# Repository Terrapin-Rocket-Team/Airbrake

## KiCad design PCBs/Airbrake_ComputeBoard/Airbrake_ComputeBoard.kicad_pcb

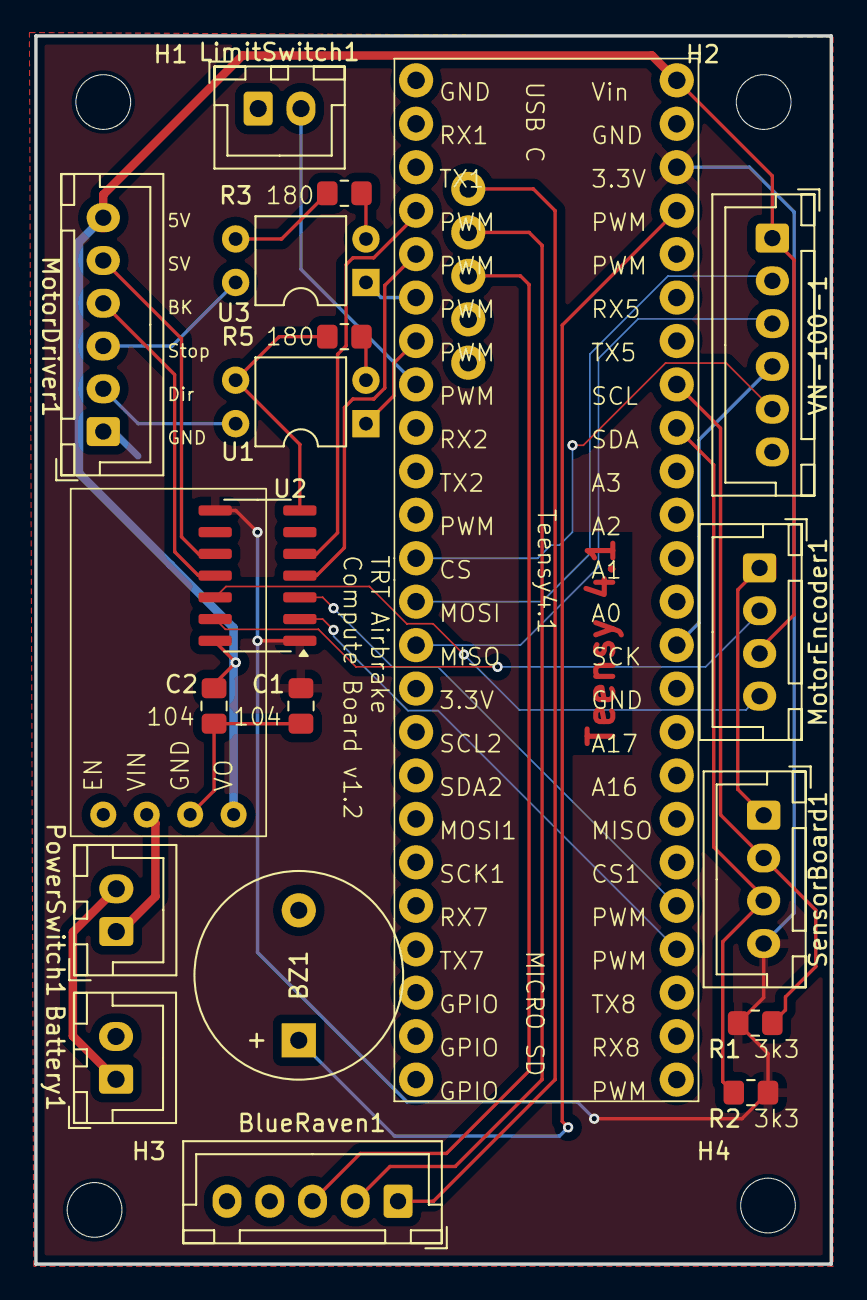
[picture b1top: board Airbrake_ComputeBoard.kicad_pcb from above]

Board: 2 copper layers, 46.5 x 71.8 mm, 24 parts (0 on the bottom side), 30 nets.

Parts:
BZ1: Buzzer; Buzzer_12x9.5RM7.6
Battery1: Conn_01x02; JST_XH_B2B-XH-A_1x02_P2.50mm_Vertical
BlueRaven1: Conn_01x05; JST_XH_B5B-XH-A_1x05_P2.50mm_Vertical
Buck_Converter1: Buck_Converter
C1, C2: 0.1µF; C_0805_2012Metric_Pad1.18x1.45mm_HandSolder
H1, H2, H3, H4: MountingHole; MountingHole_3.2mm_M3
LimitSwitch1: Conn_01x02; JST_XH_B2B-XH-A_1x02_P2.50mm_Vertical
MotorDriver1: Conn_01x06; JST_XH_B6B-XH-A_1x06_P2.50mm_Vertical
MotorEncoder1: Conn_01x04; JST_XH_B4B-XH-A_1x04_P2.50mm_Vertical
PowerSwitch1: Conn_01x02; JST_XH_B2B-XH-A_1x02_P2.50mm_Vertical
R1, R2: 3.3kΩ; R_0805_2012Metric_Pad1.20x1.40mm_HandSolder
R3, R5: 180Ω; R_0805_2012Metric_Pad1.20x1.40mm_HandSolder
SensorBoard1: Conn_01x04; JST_XH_B4B-XH-A_1x04_P2.50mm_Vertical
Teensy4.1: Teensy_4.1_USB
U1, U3: PC817; DIP-4_W7.62mm
U2: TXB0104D; SOIC-14_3.9x8.7mm_P1.27mm
VN-100-1: Conn_01x06; JST_XH_B6B-XH-A_1x06_P2.50mm_Vertical

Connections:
+3.3V: C1.1, R1.2, R2.1, SensorBoard1.4, Teensy4.1.45 (3.3V), U2.1 (VCCA), U2.8 (OE)
+5V: Buck_Converter1.3 (VO), C2.1, MotorDriver1.6, MotorEncoder1.3, Teensy4.1.47 (Vin), U2.14 (VCCB), VN-100-1.1
/BK: Teensy4.1.4 (PWM), U2.4 (A3)
/BK_5V: MotorDriver1.4, U2.11 (B3)
/CS: Teensy4.1.11 (CS), VN-100-1.5
/D+: BlueRaven1.3, Teensy4.1.50 (usb_D+)
/D-: BlueRaven1.2, Teensy4.1.49 (usb_D-)
/Dir: Teensy4.1.6 (PWM), U1.1
/Dir_5V: MotorDriver1.2, U1.4
/Encoder_A: Teensy4.1.27 (PWM), U2.2 (A1)
/Encoder_A_5V: MotorEncoder1.2, U2.13 (B1)
/Encoder_B: Teensy4.1.28 (PWM), U2.3 (A2)
/Encoder_B_5V: MotorEncoder1.4, U2.12 (B2)
/Limit_Switch: LimitSwitch1.2, Teensy4.1.7 (PWM)
/MISO: Teensy4.1.13 (MISO), VN-100-1.3
/MOSI: Teensy4.1.12 (MOSI), VN-100-1.2
/SCK: Teensy4.1.34 (SCK), VN-100-1.4
/SCL: R1.1, SensorBoard1.2, Teensy4.1.40 (SCL)
/SDA: R2.2, SensorBoard1.3, Teensy4.1.39 (SDA)
/SV: Teensy4.1.3 (PWM), U2.5 (A4)
/SV_5V: MotorDriver1.5, U2.10 (B4)
/Stop: Teensy4.1.5 (PWM), U3.1
/Stop_5V: MotorDriver1.3, U3.4
/buzzer: BZ1.1 (+), Teensy4.1.44 (PWM)
/usb_5v: BlueRaven1.1, Teensy4.1.48 (usb_5v)
GND: BZ1.2 (-), Battery1.2, BlueRaven1.4, BlueRaven1.5, Buck_Converter1.2 (GND), C1.2, C2.2, LimitSwitch1.1, MotorDriver1.1, MotorEncoder1.1, R3.2, R5.2, SensorBoard1.1, Teensy4.1.0 (GND), Teensy4.1.46 (GND), Teensy4.1.51 (GND), Teensy4.1.52 (GND), U1.3, U2.7 (GND), U3.3, VN-100-1.6
unnamed: Battery1.1, PowerSwitch1.2
unnamed: Buck_Converter1.1 (VIN), PowerSwitch1.1
unnamed: R3.1, U3.2
unnamed: R5.1, U1.2

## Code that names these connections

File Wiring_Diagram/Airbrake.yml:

connectors:
  BlueRaven1:
    type: Compute Board
    subtype: Male
    pincount: 5
    pinlabels: [usb_5v, D-, D+, GND, GND]
    image:
      src: Pictures/BlueRaven1.png
      height: 100


  SensorBoard1:
    type: Compute Board
    subtype: Male
    pincount: 4
    pinlabels: [GND, SCL, SDA, +3.3V]
    image:
      src: Pictures/SensorBoard1.png
      height: 100


  MotorEncoder1:
    type: Compute Board
    subtype: Male
    pincount: 4
    pinlabels: [GND, Encoder_A, +5V, Encoder_B]
    image:
      src: Pictures/MotorEncoder1.png
      height: 100


  VN-100-1:
    type: compute Board
    subtype: Male
    pincount: 6
    pinlabels: [+5V, MOSI, MISO, SCK, SC, GND]
    image:
      src: Pictures/VN-100.png
      height: 100


  LimitSwitch1:
    type: Compute Board
    subtype: Male
    pincount: 3
    pinlabels: [GND, NC, NO]
    image:
      src: Pictures/LimitSwitch1.png
      height: 100


  MotorDriver1:
    type: Compute Board
    subtype: Male
    pincount: 6
    pinlabels: [GND, Motordriver_pin_2, Motordriver_pin_3, Motordriver_pin_4, Motordriver_pin_5, +5V]
    image:
      src: Pictures/MotorDriver1.png
      height: 100


  Battery1:
    pincount: 2
    pinlabels: [NET - (Battery1-Pin_1), GND]
    image:
      src: Pictures/Battery1.png
      height: 100
  

  PowerSwitch1:
    pincount: 2
    pinlabels: [GND, +V]


  BlueRaven:
    type: Sensor
    subtype: Micro-USB / Screw
    pincount: 7
    pinlabels: [+V, GND, APO, MAIN, 3RD, 4TH, Micro-USB]
    image:
      src: Pictures/BlueRaven.png
      height: 100


  SensorBoard:
    type: Sensor
    subtype: Male
    pincount: 4
    pinlabels: [GND, SCL, SDA, 3V3]
    image:
      src: Pictures/SensorBoard.png
      height: 80


  MotorController_IN:
    type: Controler
    subtype: Screw
    pincount: 6
    pinlabels: [5V, 0-5V, GND, DIR, BRAKE, STOP]
    image:
      src: Pictures/MotorControlerIn.png
      height: 160  # Scale the image size slightly down


  MotorController_OUT3:
    type: Controler
    subtype: Screw
    pincount: 3
    pinlabels: [MA, BA, MC]
    image:
      src: Pictures/MotorControlerOut.png
      height: 110  # Scale the image size slightly down
    

  MotorController_OUT2:
    type: Controler
    subtype: Screw
    pincount: 2
    pinlabels: [VCC, GND]
    image:
      src: Pictures/MotorControlerOut.png
      height: 110

  

  MotorController_OUT5:
    type: Controler
    subtype: pin
    pincount: 5
    pinlabels: [GND, Hc, Hb, Ha, 5V]
    image:
      src: Pictures/MotorController_Out5.png
      height: 70


  VN-100_J5:
    type: Sensor
    subtype: Male
    pincount: 30
    pinlabels: [GND, GND, GND, GND, TX2, RX2, TARE/RESTORE, NC, SYNC_OUT, WIN, ENABLE, TX1, RX1, RESV, SYNC_IN_2, SPI_SCK, SPI_MISO, REPRGM, NRST, SYNC_IN, SPI_CS, GPS_PPS, VBAT, RESV, RESV, GND, GPS_RF, GND]
    image:
      src: Pictures/Vectornav-100-c.png
      height: 135


  LimitSwitch:
    type: Sensor
    subtype: Clip
    pincount: 3
    pinlabels: [GND, NC, NO]


  Motor3:
    type: Motor
    subtype: Female
    pincount: 3
    pinlabels: [...,...,...]
    image:
      src: Pictures/Motor_connector.png
      height: 100


  Motor5:
    type: Motor
    subtype: Female
    pincount: 5
    pinlabels: [...,...,...,...,...]
    image:
      src: Pictures/Motor_connector.png
      height: 100


  MotorEncoder:
    type: sensor
    subtype: pin
    pincount: 10
    pinlabels: [GND, GND, I, I, A, A, +5V, +5V, B, B]
    image:
      src: Pictures/Motor_encoder.png
      height: 100


  Battery-1:
    pincount: 2
    pinlabels: [+V, GND]
  

  Battery-2:
    pincount: 2
    pinlabels: [+V, GND]


  Battery-3:
    pincount: 2
    pinlabels: [+V, GND]


  Screw_switch1:
    pincount: 2
    pinlabels: [+, -]


  Screw_switch2:
    pincount: 2
    pinlabels: [+, -]


  Screw_switch3:
    pincount: 2
    pinlabels: [+, -]


cables:
  W1:
    colors: [RD, WH, GY, GN, BU]
    wirecount: 5
  W2:
    colors: [BK, YE, LB, RD]
    wirecount: 4
  W3:
    colors: [OG, YE, GN, VT]
    wirecount: 4
    image:
      src: Pictures/Encoder_wire.png
      height: 100
  W4:
    colors: [RD, LB, GN, YE, WH, BK]
    wirecount: 6
  W5:
    colors: [BK,RD]
    wirecount: 2
  W6:
    colors: [YE, YE, LB, WH, YE, BK]
    wirecount: 6
  W7:
    colors: [WH, YE, LB]
    wirecount: 3
    image:
      src: Pictures/Motor_wire3.png
      height: 100
  W8:
    colors: [RD, BK]
    wirecount: 2
  W9:
    colors: [RD, BK]
    wirecount: 2
  W10:
    colors: [BK,LB,YE,OG,RD]
    wirecount: 5
    image:
      src: Pictures/Motor_wire5.png
      height: 100
  W11:
    colors: [RD,BK]
    wirecount: 2
  W12:
    colors: [BK,RD]
    wirecount: 2
  W13:
    colors: [RD,BK]
    wirecount: 2
  W14:
    colors: [RD,BK]
    wirecount: 2


connections:
 -
   - BlueRaven1: [1,2,3,4]
   - W1: [1,2,4,5]
 -
   - W1: [3]
   - BlueRaven: [7]
 -
   - SensorBoard1: [1,2,3,4]
   - W2: [1,2,3,4]
   - SensorBoard: [1,2,3,4]
 -
   - MotorEncoder1: [1,2,3,4]
   - W3: [1,2,3,4]
   - MotorEncoder: [1,5,7,9]
 -
   - VN-100-1: [1,2,3,4,5,6]
   - W4: [1,2,3,4,5,6]
   - VN-100_J5: [10, 17, 19, 16, 23, 18]
 -
   - LimitSwitch1: [1,2]
   - W5: [1,2]
   - LimitSwitch: [1,2]
 -
   - MotorDriver1: [1,2,3,4,5,6]
   - W6: [1,2,3,4,5,6]
 -
   - W6: [2,3,4,5,6]
   - MotorController_IN: [2,5,6,4,3]
 -
   - MotorController_OUT3: [1,2,3]
   - W7: [1,2,3]
   - Motor3: [1,2,3]
 -
   - Battery-1: [1,2] 
   - W8: [1,2]
   - Battery1: [1,2]
 -
   - Battery-2: [1,2]
   - W9: [1,2]
   - Screw_switch1: [1,2]
 -
   - MotorController_OUT5: [1,2,3,4,5]
   - W10: [1,2,3,4,5]
   - Motor5: [1,2,3,4,5]
 - 
   - Screw_switch1: [1,2]
   - W11: [1,2]
   - MotorController_OUT2: [1,2]
 - 
   - PowerSwitch1: [1,2]
   - W12: [1,2]
   - Screw_switch2: [2,1]
 - 
   - Battery-3: [1,2]
   - W13: [1,2]
   - Screw_switch3: [1,2]
 -
   - Screw_switch3: [1,2]
   - W14: [1,2]
   - BlueRaven: [1,2]

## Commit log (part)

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2024-06-21 FlapActuation Optimized Functions
    SAC2024 rewriting air brake code, calculating actuation angle and subsequent functions
2024-07-08 added matlab shock stuff
2024-07-08 initial start
2024-07-18 Basic Cad For New Airbrake
    Not sure if we're going to use it but the rude cad is here
2024-07-23 flap CAD and shock torque calcs
2024-07-29 created motor_parameters
2024-07-29 CAD and dimension updates
2024-08-01 gitignore
2024-08-19 moving flight code to it's own branch
2024-08-28 initial matlab
2024-08-28 added motor and drag simulation
2024-08-28 added aoa. model comleted
2024-08-29 got rid of the .asv
2024-08-31 Moved CAD
2024-09-03 made a rocket type to pass in
2024-09-10 got state estimation tester working with open rocket
2024-09-12 CAD update
2024-09-17 made kf 6 dimension state w/ 3 meas
2024-09-17 added meas data
2024-09-17 got rid of the flight code
2024-09-17 got rid of autosaves
2024-09-17 move motor_parameters to head
2024-09-17 Tentative full CAD config
2024-09-20 flight code that still doesn't build
2024-09-20 Placeholder KF
2024-09-20 Fix State code
2024-09-20 compiled code
2024-09-20 got rid of .DS_Store
2024-09-20 Revert "Moved CAD"
    This reverts commit 17623fdfb91fb210298f1cc3f48321fa1b9009fc.
2024-09-20 Revert "CAD"
    This reverts commit 8359aeebe09319ea7ef6e981cab92fe88a2f2b34.
2024-09-24 h and cpp files
2024-09-24 got rid of binary math
2024-09-24 initail test code
2024-09-24 vn brought into mmfs framework
2024-09-24 added wiring images
2024-09-24 got rid of airbrake cad
2024-09-24 got rid of cad
2024-09-24 compile updates based on mmfs 2.0.0
2024-09-24 added the current cad
2024-09-29 updated airbrake schematic
2024-09-29 created pcb footprint
2024-10-01 CAD updates
2024-10-03 pcb zip
2024-10-06 30k kf sim
2024-10-10 created motor force script
2024-10-11 fixed psi
2024-10-22 Added Teensy footprint with USB headers
2024-10-23 created compute board v1.1
2024-10-23 Updated level shifter transistors w/ resistors
    Added resistors; changed transistors from PNP to NPN; added pull up resistors to output signals.
2024-10-23 Updated PCB to add resistors to level shifters.
    Updated PCB; Added resistors
2024-10-23 final gerber generated
2024-10-24 actual ordered board
2024-10-30 kf stuff
2024-10-30 added the graph of const motor force, var drag force
2024-10-30 make graph say single flap
2024-11-20 made initial encoder class
2024-11-21 encoder updates
2024-11-22 Copied vectornav library into lib folder and added code to read delta time, theta, and velocity
2024-11-22 Added delta V and delta theta code to VN100 mmfs sensor code
2024-12-02 Initial commit to motor branch
2024-12-03 Added packed data code to VN100
2024-12-04 attached vn100 sensor to state
2024-12-04 this isn't working lol
2024-12-04 fix some erros
2024-12-04 baaba
2024-12-04 got compile
2024-12-04 cleaned up and comment airbrake code
2024-12-04 more working
2024-12-05 Added code to control flaps
2024-12-05 added input check to goToDegree
2024-12-05 added some comments
2024-12-07 flight code. vno100 fixes
2024-12-07 dec launch data
2024-12-12 added ability for multiple sensors
2024-12-14 wrote EKF part of readme
2024-12-14 added NEES graph
2024-12-17 Added optocouplers, level shifter, and connector for a limit switch
2024-12-17 Made new PCB
2024-12-19 state estimation stuff
2024-12-19 check and created gerber
2024-12-31 got it working
2025-01-04 serg
2025-01-08 velocity from blueraven
2025-01-09 Include Errors
2025-01-10 All sensor values from Blue Raven
2025-01-29 added blue raven stuff
2025-01-31 Fixed BR
2025-02-01 added a function to stop motor before switching directions
2025-02-01 flight code changes
2025-02-03 airbrake flight code that flew
2025-02-15 updated to mmfs v3.0 for the code
2025-02-18 fixed blowing up altitude
2025-02-18 updating main with contorller code
2025-02-22 added ekf
2025-02-23 compiling on v3
2025-02-23 initial airbrake kalman filter implemented
2025-02-23 added outlier rejection to the kalman filter
    making an mmfs issue for this to be done correctly
2025-02-23 looked over old airbrake functions and added airbrake specific data reporting
2025-02-24 input velocity of calc actuation angle
2025-02-24 Body Frame
2025-02-26 Better BodyFrame
2025-02-26 reviewed body frame transition
2025-02-26 Create Inital_file
2025-02-26 Added files for wiring diagram.
2025-02-26 updated main for first test of baro in HITL
2025-02-28 initial limit switch stuff
2025-02-28 fixed limit switch zeroing problem
2025-02-28 updated zero motor function to the circular buffer thingy
2025-02-28 encoder stuff
2025-02-28 MotorStopCondition
2025-03-01 updated stop to stall condition. can't have limit switch prevent moving flaps out
2025-03-01 shit is breaking
2025-03-01 set max flap angle to 70 and fixed crashing
2025-03-02 changed for hitl over serial
2025-03-02 basic changes from HITL branch
2025-03-02 75 to 70
2025-03-02 some changes
2025-03-03 code we flew in the march mdra launch
2025-03-07 hitl updates
2025-03-07 compiles
2025-03-07 propagator
2025-03-07 made some simulation updates
2025-03-07 got a good bit of the sim code done
2025-03-10 Added code to prevent NaN values and replace them with approximation until the issue is resolved
2025-03-11 Create sample
2025-03-12 Approved
2025-03-15 added tilt to the propagator
2025-03-22 added old flight data
2025-03-23 got code mostly working in a software world
2025-03-23 got first full HITL run with good values
2025-03-24 making progress. wrote down list of todos
2025-03-24 saving before moving to numpy arrarys
2025-03-24 not working
2025-03-25 orientation stuff is cursed
2025-03-26 HITL with file retreival
2025-03-26 some hitl stuff
2025-03-27 Added bluetooth
2025-03-27 full feature 1st pass
2025-03-27 commiting to fix esp things
2025-03-27 Try to fix BT
2025-03-27 minor changes
2025-03-27 BT isReady check
2025-03-28 fixed blue raven data values
2025-03-28 try to fix bluetooth
2025-03-29 trying to fix bluetooth
2025-03-29 fix vn100 and Message conflict
2025-03-29 flight code april
2025-04-29 clean up and get rid of vn
2025-04-30 cleanup cad to archive and wrote flap force in python
2025-04-30 HITL flight software and data plotting
2025-04-30 final hitl testing
2025-05-01 moved vn to vn folder
2025-05-01 reset gitignore
2025-05-14 Changed arduino string to std string
2025-05-14 Added motor speed variable in AirbreakState
2025-05-14 Added motorSpeed variable in airbrake_state.cpp
2025-05-14 Added semicolon
2025-05-22 some full interior hitl runs
2025-05-25 fix CdA estimation and add better drag calculation
2025-05-25 added mock blue raven and pressure increase shock to simulation
2025-05-31 added simple supersonic filter - complex ekf commented out
2025-06-01 fuck myself we stink
2025-06-06 trying to get ekf to work
2025-06-09 airbrake monte carlo and flight code
2025-06-09 fixed staging
2025-06-10 bluetooth ready to go?
2025-06-10 added barometric error correction
2025-06-11 final flight code
2025-06-12 flight code that we flew
2025-06-12 flap force stuff with new stronger motor
2025-10-07 basic motordriver object
2025-12-13 Motor Works
2025-12-13 idek
2025-12-31 airbrake
2026-01-02 hitl testing
2026-01-02 Added command to set angle directly
2026-01-20 HITL testing improvements
2026-02-02 fixes to get ready for integration
2026-02-11 Added Controller and Barometer logic NOT TESTED
2026-02-13 feat(airbrake): integrate SITL airbrake sim and native motor mock
2026-02-13 work on SITL
2026-02-13 more fixes
2026-02-13 fixes to HITL/SITL
2026-02-13 pushe and kp ki
2026-02-13 orientation viewer
2026-02-14 mag calibration + mahoney
2026-02-14 fixed_values
2026-02-17 Added Motor Logic and Functions
    Added functions to idle and turn on the motor. Used those function in airbrakecontroller.cpp to idle the motor until the controller is in boost.
2026-02-17 Was going to launch Feb 14th
2026-02-19 Changes for Comments in PR
    Added the changes based on Drew's comments in the PR.
2026-02-19 Motor new enables and zeroes on boost.
    When the controller detects boost, the motor will now enable and run the zero function.
2026-02-20 updates for new hardware
2026-02-25 Motor Enables for setPos() and setVel()
    Whenever the commands to change the position of the flaps and the speed of motor is called, it ensures the motor is enabled first so movement can be made.
2026-02-25 No motor zero on boost
    The motor no longer zeroes when boost is first detected. It will only enable the motor when boost is detected.
2026-02-25 Revert "Motor Enables for setPos() and setVel()"
    This reverts commit 265bfe16242f99d785db1bc10c2e1024900fe05f.
2026-02-25 Enables motor in movement command in main
    In main.cpp, when flap angle is attempted to change, enables the motor if it is not already.
2026-02-26 botlimitswitchadded
2026-02-26 fixed imu and mag orientation
2026-02-26 init dev env for nixos+nvim+clangd
    my name is devin and i have special needs that you will all follow :3c
2026-02-27 some minor improvements to remove some AI slop
2026-02-27 Removed a lot of AI slop
2026-02-27 Building
2026-02-28 fixes and changes
2026-03-02 launch code
2026-03-06 wind tunnel
2026-03-14 SITL is mostly working
2026-03-14 Refactor AirbrakeController and main setup for improved rocket state handling and sensor integration
2026-03-15 index on wind-tunnel: c4c8eb0 Refactor AirbrakeController and main setup for improved rocket state handling and sensor integration
2026-03-15 untracked files on wind-tunnel: c4c8eb0 Refactor AirbrakeController and main setup for improved rocket state handling and sensor integration
2026-03-15 Refactor flight code and enhance sensor integration
    - Updated `propagator.py` to use the `ambiance` library for atmospheric calculations, improving accuracy.
    - Adjusted rocket parameters including total impulse and burn time for better performance.
    - Modified drag coefficient calculation to use a fixed value instead of a dynamic function.
    - Changed airbrake controller parameters for improved responsiveness and accuracy in flight.
    - Introduced new sensor classes (`BGHGAccel`, `BRAccel`, `BRBaro`, `BRIMU`) for better modularity and integration with the Blue Raven system.
    - Implemented `BlueRaven` class to handle data ingestion and processing from sensors, enhancing data management.
2026-03-16 Enhance BlueRaven sensor integration and update flight parameters for improved rocket performance
2026-03-18 Add avionics packet protocol and implement packet stream handling for telemetry data
2026-03-18 Refactor: Move MessageHandlers and PacketStreams to Helpers
    - Deleted old MessageHandlers.h and MessageHandlers.cpp files.
    - Created new MessageHandlers.h and MessageHandlers.cpp in the Helpers directory.
    - Deleted old PacketStreams.h and PacketStreams.cpp files.
    - Created new PacketStreams.h and PacketStreams.cpp in the Helpers directory.
    - Updated main.cpp to include new headers and adjust references accordingly.
    - Refactored RuntimeHelpers to include necessary dependencies and moved to Helpers.
2026-03-18 Enhance simulation accuracy by refining inertial acceleration handling and updating update rate to 20Hz
2026-03-19 Dannys weird stuff before kansas
2026-03-19 Refactor: Update pressure handling in FlightCodePropagatorSim and adjust update rate to 10Hz
2026-03-19 Refactor code structure for improved readability and maintainability
2026-03-19 weight change and final hitl before kansas
2026-03-20 add sending radiomessage over serial
